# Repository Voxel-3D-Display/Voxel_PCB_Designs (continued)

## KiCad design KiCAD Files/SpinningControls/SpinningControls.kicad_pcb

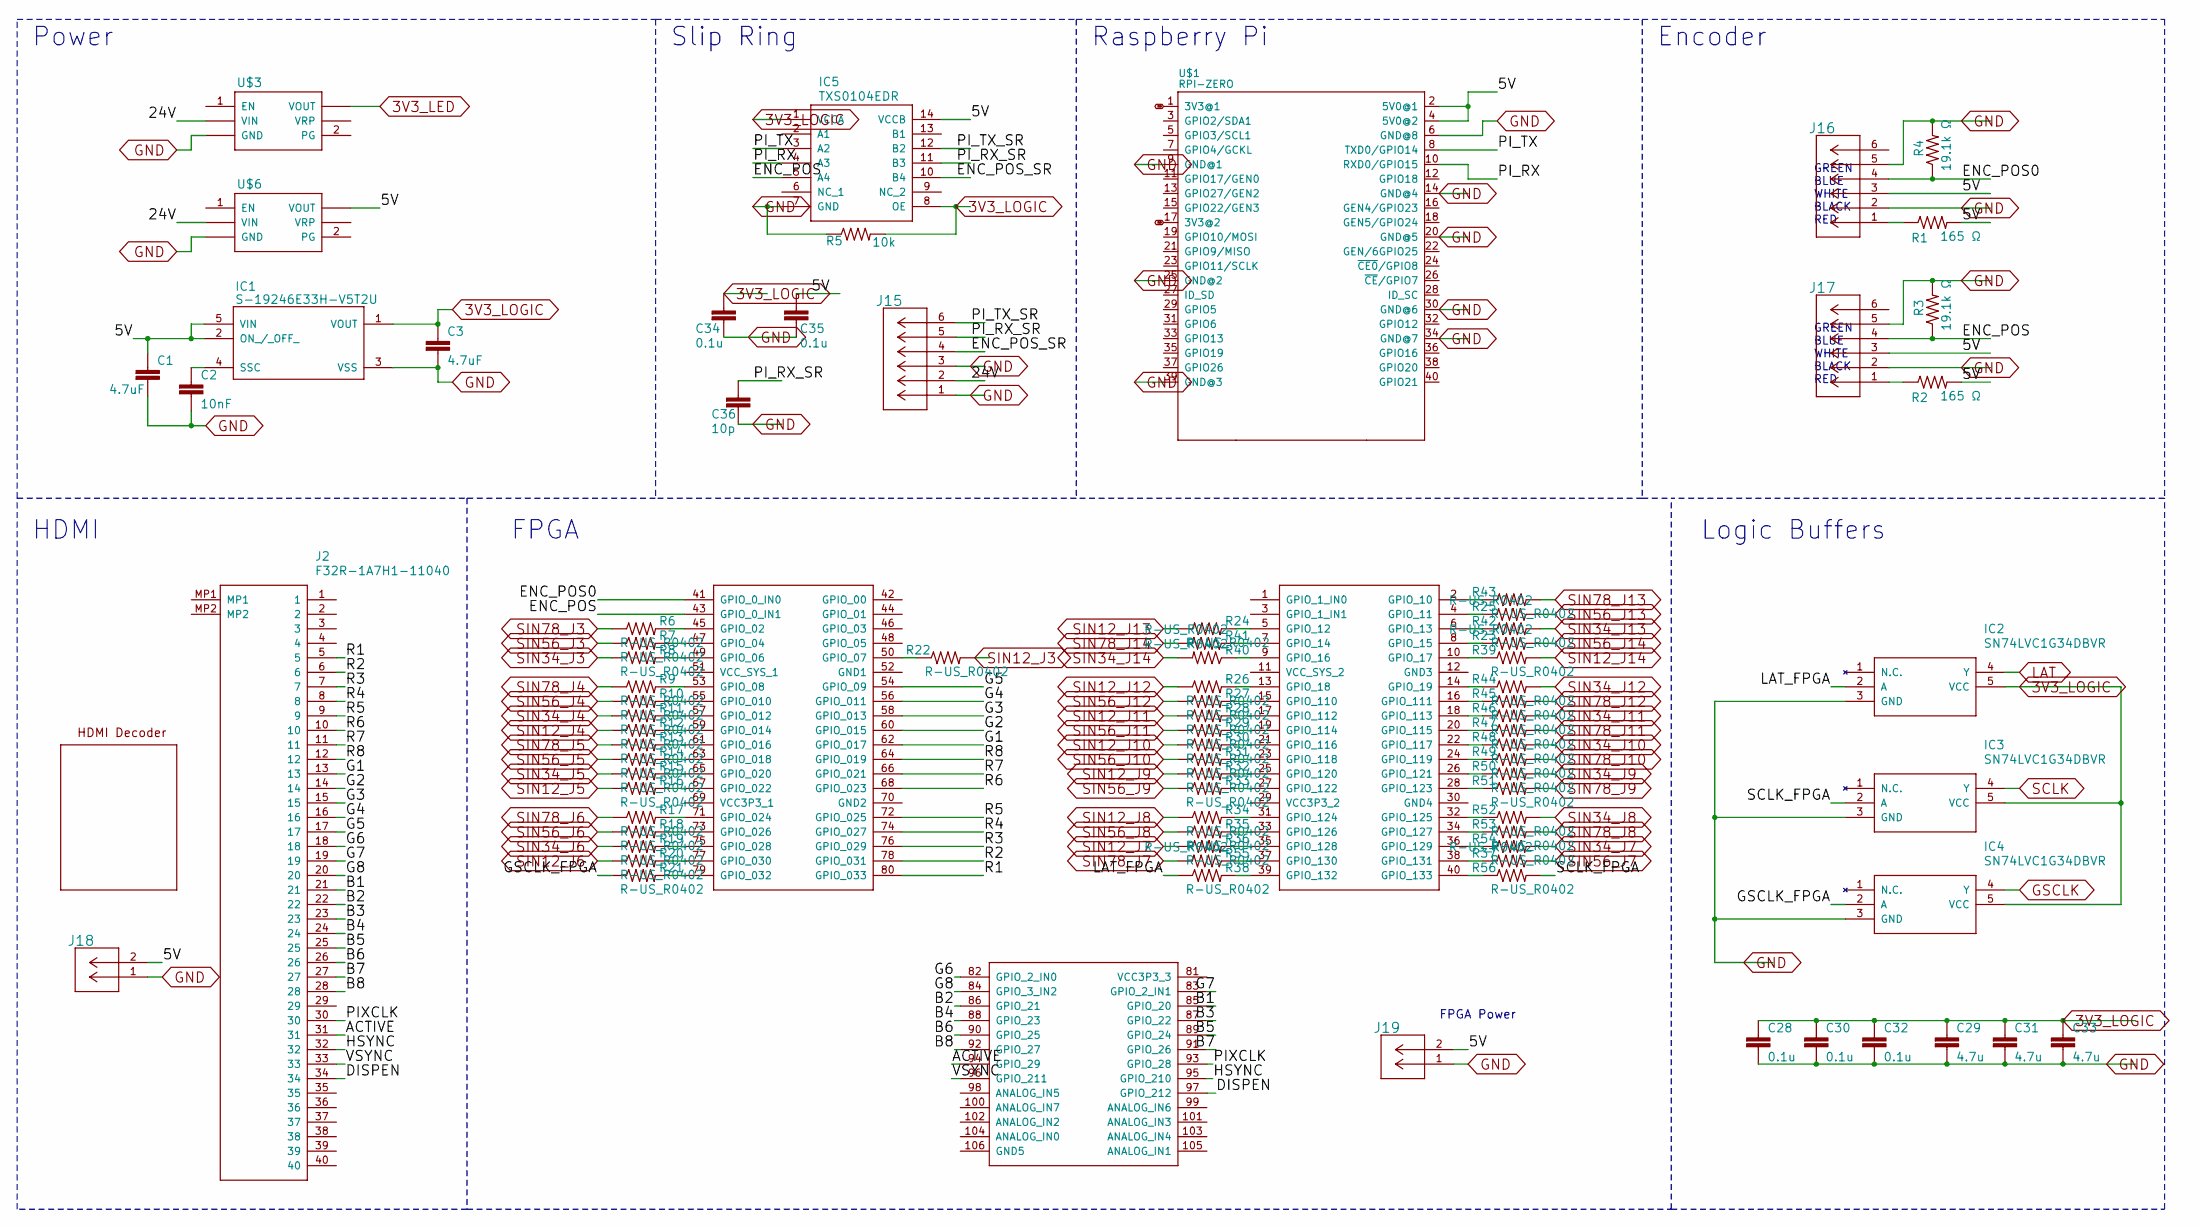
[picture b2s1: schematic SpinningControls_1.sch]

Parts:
C1, C3: 4.7uF; C0603
C2: 10nF; C0603
C28, C30, C32, C34, C35: 0.1u; C0603
C29, C31, C33: 4.7u; C0603
C36: 10p; C0603
FPGA: DE0-NANO
IC1: S-19246E33H-V5T2U; S19246E33HV5T2U
IC2, IC3, IC4: SN74LVC1G34DBVR; SOT95P280X145-5N
IC5: TXS0104EDR; SOIC127P600X175-14N
J2: F32R-1A7H1-11040; F32R1A7H111040
J15, J16, J17: 430450612; CON_430450612_MOL
J18, J19: 436500215; CON_436500215_MOL
R1, R2: 165 Ω; R0603
R3, R4: 19.1k Ω; R0603
R5: 10k; R0603
R6, R7, R8, R9, R10, R11, R12, R13, R14, R15, R16, R17, R18, R19, R20, R21, R22, R23, R24, R25, R26, R27, R28, R29, R30, R31, R32, R33, R34, R35, R36, R37, R38, R39, R40, R41, R42, R43, R44, R45, R46, R47, R48, R49, R50, R51, R52, R53, R54, R55, R56: R-US_R0402; R0402
U$1: RPI-ZERO; RASPBERRYPI_BASTELSTUBE_V13_RASPI_BOARD_B+_FULL
U$2: TFP401
U$3: 3V3_BUCK_REGULATOR; 2X06
U$6: 5V_BUCK_REGULATOR; 2X06

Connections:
3V3: U$1.1 (3V3@1), U$1.17 (3V3@2)
3V3_LED: U$3.11 (VOUT), U$3.12 (VOUT); also elsewhere on the board
3V3_LOGIC: C3.1, C28.1, C29.1, C30.1, C31.1, C32.1, C33.1, C34.1, IC1.1 (VOUT), IC2.5 (VCC), IC3.5 (VCC), IC4.5 (VCC), IC5.1 (VCCA), IC5.8 (OE), R5.2; also elsewhere on the board
/SpinningControls_1/5V: C1.1, C35.1, IC1.2 (ON_/_OFF_), IC1.5 (VIN), IC5.14 (VCCB), J16.3, J17.3, J18.2, J19.2, R1.2, R2.2, U$1.2 (5V0@1), U$1.4 (5V0@2), U$6.11 (VOUT), U$6.12 (VOUT)
/SpinningControls_1/24V: J15.2, U$3.5 (VIN), U$3.6 (VIN), U$6.5 (VIN), U$6.6 (VIN)
/SpinningControls_1/ACTIVE: J2.31; also elsewhere on the board
/SpinningControls_1/B1: J2.21; also elsewhere on the board
/SpinningControls_1/B2: J2.22; also elsewhere on the board
/SpinningControls_1/B3: J2.23; also elsewhere on the board
/SpinningControls_1/B4: J2.24; also elsewhere on the board
/SpinningControls_1/B5: J2.25; also elsewhere on the board
/SpinningControls_1/B6: J2.26; also elsewhere on the board
/SpinningControls_1/B7: J2.27; also elsewhere on the board
/SpinningControls_1/B8: J2.28; also elsewhere on the board
/SpinningControls_1/DISPEN: J2.34; also elsewhere on the board
/SpinningControls_1/ENC_POS: IC5.5 (A4), J17.4, R3.1; also elsewhere on the board
/SpinningControls_1/ENC_POS0: J16.4, R4.1; also elsewhere on the board
/SpinningControls_1/ENC_POS_SR: IC5.10 (B4), J15.4
/SpinningControls_1/G1: J2.13; also elsewhere on the board
/SpinningControls_1/G2: J2.14; also elsewhere on the board
/SpinningControls_1/G3: J2.15; also elsewhere on the board
/SpinningControls_1/G4: J2.16; also elsewhere on the board
/SpinningControls_1/G5: J2.17; also elsewhere on the board
/SpinningControls_1/G6: J2.18; also elsewhere on the board
/SpinningControls_1/G7: J2.19; also elsewhere on the board
/SpinningControls_1/G8: J2.20; also elsewhere on the board
/SpinningControls_1/GSCLK_FPGA: IC4.2 (A), R21.1
/SpinningControls_1/HSYNC: J2.32; also elsewhere on the board
/SpinningControls_1/LAT_FPGA: IC2.2 (A), R38.1
/SpinningControls_1/PIXCLK: J2.30; also elsewhere on the board
/SpinningControls_1/PI_RX: IC5.4 (A3), U$1.10 (RXD0/GPIO15)
/SpinningControls_1/PI_RX_SR: C36.1, IC5.11 (B3), J15.5
/SpinningControls_1/PI_TX: IC5.3 (A2), U$1.8 (TXD0/GPIO14)
/SpinningControls_1/PI_TX_SR: IC5.12 (B2), J15.6
/SpinningControls_1/R1: J2.5; also elsewhere on the board
/SpinningControls_1/R2: J2.6; also elsewhere on the board
/SpinningControls_1/R3: J2.7; also elsewhere on the board
/SpinningControls_1/R4: J2.8; also elsewhere on the board
/SpinningControls_1/R5: J2.9; also elsewhere on the board
/SpinningControls_1/R6: J2.10; also elsewhere on the board
/SpinningControls_1/R7: J2.11; also elsewhere on the board
/SpinningControls_1/R8: J2.12; also elsewhere on the board
/SpinningControls_1/SCLK_FPGA: IC3.2 (A), R56.2
/SpinningControls_1/VSYNC: J2.33; also elsewhere on the board
GND: C1.2, C2.2, C3.2, C28.2, C29.2, C30.2, C31.2, C32.2, C33.2, C34.2, C35.2, C36.2, IC1.3 (VSS), IC2.3 (GND), IC3.3 (GND), IC4.3 (GND), IC5.7 (GND), J15.1, J15.3, J16.2, J16.5, J17.2, J17.5, J18.1, J19.1, R3.2, R4.2, R5.1, U$1.6 (GND@8), U$1.9 (GND@1), U$1.14 (GND@4), U$1.20 (GND@5), U$1.25 (GND@2), U$1.30 (GND@6), U$1.34 (GND@7), U$1.39 (GND@3), U$3.7 (GND), U$3.8 (GND), U$3.9 (GND), U$3.10 (GND), U$6.7 (GND), U$6.8 (GND), U$6.9 (GND), U$6.10 (GND); also elsewhere on the board
GSCLK: IC4.4 (Y); also elsewhere on the board
LAT: IC2.4 (Y); also elsewhere on the board
unnamed: C2.1, IC1.4 (SSC)
unnamed 49: R43.1; also elsewhere on the board
unnamed 51: R25.2; also elsewhere on the board
unnamed 52: R24.2; also elsewhere on the board
unnamed 53: R42.1; also elsewhere on the board
unnamed 54: R41.1; also elsewhere on the board
unnamed 55: R23.2; also elsewhere on the board
unnamed 56: R40.1; also elsewhere on the board
unnamed 57: R39.1; also elsewhere on the board
unnamed 60: R26.2; also elsewhere on the board
unnamed 61: R44.1; also elsewhere on the board
unnamed 62: R27.2; also elsewhere on the board
unnamed 63: R45.1; also elsewhere on the board
unnamed 64: R28.2; also elsewhere on the board
unnamed 65: R46.1; also elsewhere on the board
unnamed 66: R29.2; also elsewhere on the board
unnamed 67: R47.1; also elsewhere on the board
unnamed 68: R30.2; also elsewhere on the board
unnamed 69: R48.1; also elsewhere on the board
unnamed 70: R31.2; also elsewhere on the board
unnamed 71: R49.1; also elsewhere on the board
unnamed 72: R32.2; also elsewhere on the board
unnamed 73: R50.1; also elsewhere on the board
unnamed 74: R33.2; also elsewhere on the board
unnamed 75: R51.1; also elsewhere on the board
unnamed 78: R34.2; also elsewhere on the board
unnamed 79: R52.1; also elsewhere on the board
unnamed 80: R35.2; also elsewhere on the board
unnamed 81: R53.1; also elsewhere on the board
unnamed 82: R36.2; also elsewhere on the board
unnamed 83: R54.1; also elsewhere on the board
unnamed 84: R55.1; also elsewhere on the board
unnamed 85: R37.2; also elsewhere on the board
unnamed 86: R38.2; also elsewhere on the board
unnamed 87: R56.1; also elsewhere on the board
unnamed 90: R6.2; also elsewhere on the board
unnamed 92: R7.2; also elsewhere on the board
unnamed 94: R8.2; also elsewhere on the board
unnamed 95: R22.1; also elsewhere on the board
unnamed 98: R9.2; also elsewhere on the board
unnamed 99: R10.2; also elsewhere on the board
unnamed 100: R11.2; also elsewhere on the board
unnamed 101: R12.2; also elsewhere on the board
unnamed 102: R13.2; also elsewhere on the board
unnamed 103: R14.2; also elsewhere on the board
unnamed 104: R15.2; also elsewhere on the board
unnamed 105: R16.2; also elsewhere on the board
unnamed 108: R17.2; also elsewhere on the board
unnamed 109: R18.2; also elsewhere on the board
unnamed 110: R19.2; also elsewhere on the board
unnamed 111: R20.2; also elsewhere on the board
unnamed 112: R21.2; also elsewhere on the board
unnamed: J16.1, R1.1
unnamed: J17.1, R2.1
unnamed: U$3.3 (VRP), U$3.4 (VRP)
unnamed: U$6.3 (VRP), U$6.4 (VRP)
SCLK: IC3.4 (Y); also elsewhere on the board
SIN12_J3: R22.2; also elsewhere on the board
SIN12_J4: R12.1; also elsewhere on the board
SIN12_J5: R16.1; also elsewhere on the board
SIN12_J6: R20.1; also elsewhere on the board
SIN12_J7: R36.1; also elsewhere on the board
SIN12_J8: R34.1; also elsewhere on the board
SIN12_J9: R32.1; also elsewhere on the board
SIN12_J10: R30.1; also elsewhere on the board
SIN12_J11: R28.1; also elsewhere on the board
SIN12_J12: R26.1; also elsewhere on the board
SIN12_J13: R24.1; also elsewhere on the board
SIN12_J14: R39.2; also elsewhere on the board
SIN34_J3: R8.1; also elsewhere on the board
SIN34_J4: R11.1; also elsewhere on the board
SIN34_J5: R15.1; also elsewhere on the board
SIN34_J6: R19.1; also elsewhere on the board
SIN34_J7: R54.2; also elsewhere on the board
SIN34_J8: R52.2; also elsewhere on the board
SIN34_J9: R50.2; also elsewhere on the board
SIN34_J10: R48.2; also elsewhere on the board
SIN34_J11: R46.2; also elsewhere on the board
SIN34_J12: R44.2; also elsewhere on the board
SIN34_J13: R42.2; also elsewhere on the board
SIN34_J14: R40.2; also elsewhere on the board
SIN56_J3: R7.1; also elsewhere on the board
SIN56_J4: R10.1; also elsewhere on the board
SIN56_J5: R14.1; also elsewhere on the board
SIN56_J6: R18.1; also elsewhere on the board
SIN56_J7: R37.1; also elsewhere on the board
SIN56_J8: R35.1; also elsewhere on the board
SIN56_J9: R33.1; also elsewhere on the board
SIN56_J10: R31.1; also elsewhere on the board
SIN56_J11: R29.1; also elsewhere on the board
SIN56_J12: R27.1; also elsewhere on the board
SIN56_J13: R25.1; also elsewhere on the board
SIN56_J14: R23.1; also elsewhere on the board
SIN78_J3: R6.1; also elsewhere on the board
SIN78_J4: R9.1; also elsewhere on the board
SIN78_J5: R13.1; also elsewhere on the board
SIN78_J6: R17.1; also elsewhere on the board
SIN78_J7: R55.2; also elsewhere on the board
SIN78_J8: R53.2; also elsewhere on the board
SIN78_J9: R51.2; also elsewhere on the board
SIN78_J10: R49.2; also elsewhere on the board
SIN78_J11: R47.2; also elsewhere on the board
SIN78_J12: R45.2; also elsewhere on the board
SIN78_J13: R43.2; also elsewhere on the board
SIN78_J14: R41.2; also elsewhere on the board

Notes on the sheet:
FPGA Power
GREEN BLUE WHITE BLACK RED
Raspberry Pi
Encoder
Slip Ring
Power
HDMI
FPGA
Logic Buffers

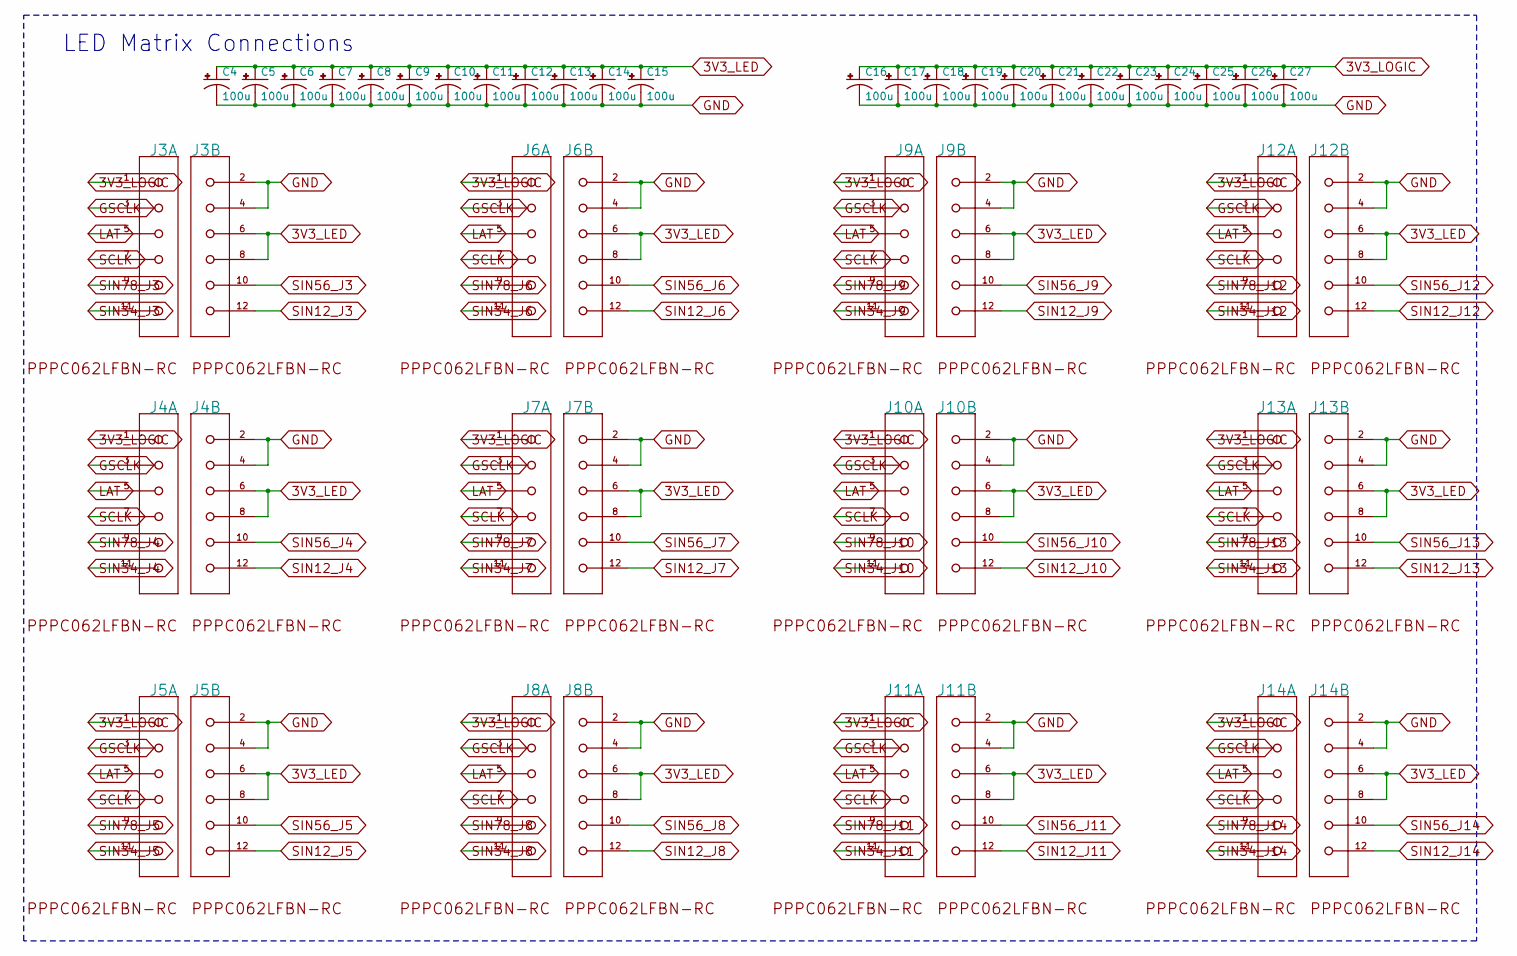
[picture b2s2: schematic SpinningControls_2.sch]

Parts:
C4, C5, C6, C7, C8, C9, C10, C11, C12, C13, C14, C15, C16, C17, C18, C19, C20, C21, C22, C23, C24, C25, C26, C27: 100u; E2-5
J3, J4, J5, J6, J7, J8, J9, J10, J11, J12, J13, J14: SULLINS_PPPC062LFBN-RCSULLINS_PPPC062LFBN-RC_0_0; SULLINS_PPPC062LFBN-RC_0

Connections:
3V3_LED: C4.+, C5.+, C6.+, C7.+, C8.+, C9.+, C10.+, C11.+, C12.+, C13.+, C14.+, C15.+, J3.6, J3.8, J4.6, J4.8, J5.6, J5.8, J6.6, J6.8, J7.6, J7.8, J8.6, J8.8, J9.6, J9.8, J10.6, J10.8, J11.6, J11.8, J12.6, J12.8, J13.6, J13.8, J14.6, J14.8; also elsewhere on the board
3V3_LOGIC: C16.+, C17.+, C18.+, C19.+, C20.+, C21.+, C22.+, C23.+, C24.+, C25.+, C26.+, C27.+, J3.1, J4.1, J5.1, J6.1, J7.1, J8.1, J9.1, J10.1, J11.1, J12.1, J13.1, J14.1; also elsewhere on the board
GND: C4.-, C5.-, C6.-, C7.-, C8.-, C9.-, C10.-, C11.-, C12.-, C13.-, C14.-, C15.-, C16.-, C17.-, C18.-, C19.-, C20.-, C21.-, C22.-, C23.-, C24.-, C25.-, C26.-, C27.-, J3.2, J3.4, J4.2, J4.4, J5.2, J5.4, J6.2, J6.4, J7.2, J7.4, J8.2, J8.4, J9.2, J9.4, J10.2, J10.4, J11.2, J11.4, J12.2, J12.4, J13.2, J13.4, J14.2, J14.4; also elsewhere on the board
GSCLK: J3.3, J4.3, J5.3, J6.3, J7.3, J8.3, J9.3, J10.3, J11.3, J12.3, J13.3, J14.3; also elsewhere on the board
LAT: J3.5, J4.5, J5.5, J6.5, J7.5, J8.5, J9.5, J10.5, J11.5, J12.5, J13.5, J14.5; also elsewhere on the board
SCLK: J3.7, J4.7, J5.7, J6.7, J7.7, J8.7, J9.7, J10.7, J11.7, J12.7, J13.7, J14.7; also elsewhere on the board
SIN12_J3: J3.12; also elsewhere on the board
SIN12_J4: J4.12; also elsewhere on the board
SIN12_J5: J5.12; also elsewhere on the board
SIN12_J6: J6.12; also elsewhere on the board
SIN12_J7: J7.12; also elsewhere on the board
SIN12_J8: J8.12; also elsewhere on the board
SIN12_J9: J9.12; also elsewhere on the board
SIN12_J10: J10.12; also elsewhere on the board
SIN12_J11: J11.12; also elsewhere on the board
SIN12_J12: J12.12; also elsewhere on the board
SIN12_J13: J13.12; also elsewhere on the board
SIN12_J14: J14.12; also elsewhere on the board
SIN34_J3: J3.11; also elsewhere on the board
SIN34_J4: J4.11; also elsewhere on the board
SIN34_J5: J5.11; also elsewhere on the board
SIN34_J6: J6.11; also elsewhere on the board
SIN34_J7: J7.11; also elsewhere on the board
SIN34_J8: J8.11; also elsewhere on the board
SIN34_J9: J9.11; also elsewhere on the board
SIN34_J10: J10.11; also elsewhere on the board
SIN34_J11: J11.11; also elsewhere on the board
SIN34_J12: J12.11; also elsewhere on the board
SIN34_J13: J13.11; also elsewhere on the board
SIN34_J14: J14.11; also elsewhere on the board
SIN56_J3: J3.10; also elsewhere on the board
SIN56_J4: J4.10; also elsewhere on the board
SIN56_J5: J5.10; also elsewhere on the board
SIN56_J6: J6.10; also elsewhere on the board
SIN56_J7: J7.10; also elsewhere on the board
SIN56_J8: J8.10; also elsewhere on the board
SIN56_J9: J9.10; also elsewhere on the board
SIN56_J10: J10.10; also elsewhere on the board
SIN56_J11: J11.10; also elsewhere on the board
SIN56_J12: J12.10; also elsewhere on the board
SIN56_J13: J13.10; also elsewhere on the board
SIN56_J14: J14.10; also elsewhere on the board
SIN78_J3: J3.9; also elsewhere on the board
SIN78_J4: J4.9; also elsewhere on the board
SIN78_J5: J5.9; also elsewhere on the board
SIN78_J6: J6.9; also elsewhere on the board
SIN78_J7: J7.9; also elsewhere on the board
SIN78_J8: J8.9; also elsewhere on the board
SIN78_J9: J9.9; also elsewhere on the board
SIN78_J10: J10.9; also elsewhere on the board
SIN78_J11: J11.9; also elsewhere on the board
SIN78_J12: J12.9; also elsewhere on the board
SIN78_J13: J13.9; also elsewhere on the board
SIN78_J14: J14.9; also elsewhere on the board

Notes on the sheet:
LED Matrix Connections

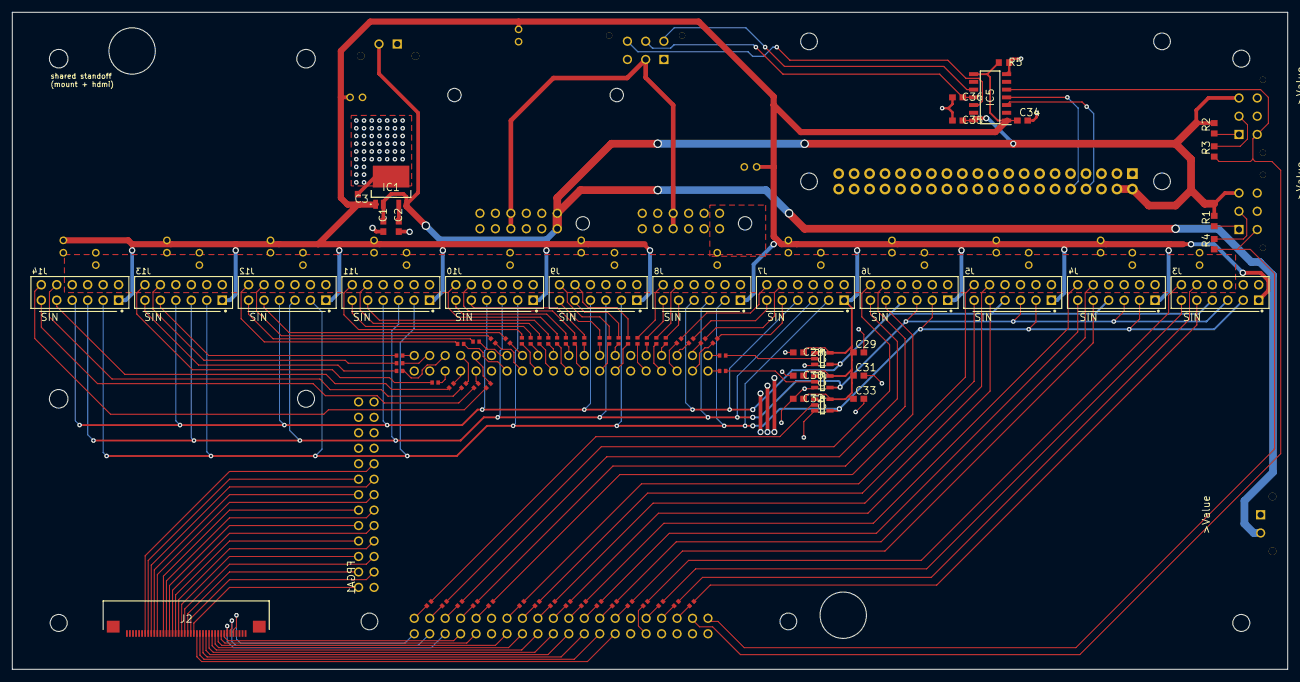
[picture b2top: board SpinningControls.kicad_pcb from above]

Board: 2 copper layers, 209.6 x 108.0 mm, 125 parts (0 on the bottom side), 152 nets.

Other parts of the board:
@HOLE0, @HOLE1, @HOLE2, @HOLE3, @HOLE4: (no value)
FPGA1: DE0-NANO

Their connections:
/SpinningControls_1/ACTIVE: FPGA1.94; also elsewhere on the board
/SpinningControls_1/B1: FPGA1.85; also elsewhere on the board
/SpinningControls_1/B2: FPGA1.86; also elsewhere on the board
/SpinningControls_1/B3: FPGA1.87; also elsewhere on the board
/SpinningControls_1/B4: FPGA1.88; also elsewhere on the board
/SpinningControls_1/B5: FPGA1.89; also elsewhere on the board
/SpinningControls_1/B6: FPGA1.90; also elsewhere on the board
/SpinningControls_1/B7: FPGA1.91; also elsewhere on the board
/SpinningControls_1/B8: FPGA1.92; also elsewhere on the board
/SpinningControls_1/DISPEN: FPGA1.97; also elsewhere on the board
/SpinningControls_1/ENC_POS: FPGA1.43; also elsewhere on the board
/SpinningControls_1/ENC_POS0: FPGA1.41; also elsewhere on the board
/SpinningControls_1/G1: FPGA1.62; also elsewhere on the board
/SpinningControls_1/G2: FPGA1.60; also elsewhere on the board
/SpinningControls_1/G3: FPGA1.58; also elsewhere on the board
/SpinningControls_1/G4: FPGA1.56; also elsewhere on the board
/SpinningControls_1/G5: FPGA1.54; also elsewhere on the board
/SpinningControls_1/G6: FPGA1.82; also elsewhere on the board
/SpinningControls_1/G7: FPGA1.83; also elsewhere on the board
/SpinningControls_1/G8: FPGA1.84; also elsewhere on the board
/SpinningControls_1/HSYNC: FPGA1.95; also elsewhere on the board
/SpinningControls_1/PIXCLK: FPGA1.93; also elsewhere on the board
/SpinningControls_1/R1: FPGA1.80; also elsewhere on the board
/SpinningControls_1/R2: FPGA1.78; also elsewhere on the board
/SpinningControls_1/R3: FPGA1.76; also elsewhere on the board
/SpinningControls_1/R4: FPGA1.74; also elsewhere on the board
/SpinningControls_1/R5: FPGA1.72; also elsewhere on the board
/SpinningControls_1/R6: FPGA1.68; also elsewhere on the board
/SpinningControls_1/R7: FPGA1.66; also elsewhere on the board
/SpinningControls_1/R8: FPGA1.64; also elsewhere on the board
/SpinningControls_1/VSYNC: FPGA1.96; also elsewhere on the board
unnamed 49: FPGA1.2; also elsewhere on the board
unnamed 51: FPGA1.4; also elsewhere on the board
unnamed 52: FPGA1.5; also elsewhere on the board
unnamed 53: FPGA1.6; also elsewhere on the board
unnamed 54: FPGA1.7; also elsewhere on the board
unnamed 55: FPGA1.8; also elsewhere on the board
unnamed 56: FPGA1.9; also elsewhere on the board
unnamed 57: FPGA1.10; also elsewhere on the board
unnamed 60: FPGA1.13; also elsewhere on the board
unnamed 61: FPGA1.14; also elsewhere on the board
unnamed 62: FPGA1.15; also elsewhere on the board
unnamed 63: FPGA1.16; also elsewhere on the board
unnamed 64: FPGA1.17; also elsewhere on the board
unnamed 65: FPGA1.18; also elsewhere on the board
unnamed 66: FPGA1.19; also elsewhere on the board
unnamed 67: FPGA1.20; also elsewhere on the board
unnamed 68: FPGA1.21; also elsewhere on the board
unnamed 69: FPGA1.22; also elsewhere on the board
unnamed 70: FPGA1.23; also elsewhere on the board
unnamed 71: FPGA1.24; also elsewhere on the board
unnamed 72: FPGA1.25; also elsewhere on the board
unnamed 73: FPGA1.26; also elsewhere on the board
unnamed 74: FPGA1.27; also elsewhere on the board
unnamed 75: FPGA1.28; also elsewhere on the board
unnamed 78: FPGA1.31; also elsewhere on the board
unnamed 79: FPGA1.32; also elsewhere on the board
unnamed 80: FPGA1.33; also elsewhere on the board
unnamed 81: FPGA1.34; also elsewhere on the board
unnamed 82: FPGA1.35; also elsewhere on the board
unnamed 83: FPGA1.36; also elsewhere on the board
unnamed 84: FPGA1.37; also elsewhere on the board
unnamed 85: FPGA1.38; also elsewhere on the board
unnamed 86: FPGA1.39; also elsewhere on the board
unnamed 87: FPGA1.40; also elsewhere on the board
unnamed 90: FPGA1.45; also elsewhere on the board
unnamed 92: FPGA1.47; also elsewhere on the board
unnamed 94: FPGA1.49; also elsewhere on the board
unnamed 95: FPGA1.50; also elsewhere on the board
unnamed 98: FPGA1.53; also elsewhere on the board
unnamed 99: FPGA1.55; also elsewhere on the board
unnamed 100: FPGA1.57; also elsewhere on the board
unnamed 101: FPGA1.59; also elsewhere on the board
unnamed 102: FPGA1.61; also elsewhere on the board
unnamed 103: FPGA1.63; also elsewhere on the board
unnamed 104: FPGA1.65; also elsewhere on the board
unnamed 105: FPGA1.67; also elsewhere on the board
unnamed 108: FPGA1.71; also elsewhere on the board
unnamed 109: FPGA1.73; also elsewhere on the board
unnamed 110: FPGA1.75; also elsewhere on the board
unnamed 111: FPGA1.77; also elsewhere on the board
unnamed 112: FPGA1.79; also elsewhere on the board

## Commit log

2021-10-13 Initial High Density PCB
2021-10-21 Automated Python scripts and one block of LED matrix
    Added a bunch of python scripts for automating Eagle design. Created a template for one LED driver block of board (to be copied later)
2021-10-28 added pictures of led matrix pcbs
2021-11-06 Finished placing all LEDs and Led Drivers
2021-11-06 Routed all the signals from the FPGA
2021-11-10 Finished routing traces on high density matrix PCB
2021-11-10 High density PCB fixes
    Fixed airwires errors and grouped components on schematic
2022-01-14 Finalized LED Matrix schematic and board files
2022-01-14 gerber files generated; cleanup
2022-01-15 fixed problem of not having pairs of drivers daisy-chained
2022-01-22 created rev2 for high density led matrix PCB
2022-01-22 lib additions for controls pcb
2022-01-22 Added RasPi EAGLE Lib
2022-01-23 Added Pololu buck regulators
2022-01-23 more lib additions
2022-01-23 Added DE0-Nano
2022-01-23 Added logic buffer
2022-01-23 power schematic and library additions
2022-01-24 finished rev 2 of PCB submatrix led
2022-01-30 controls layout partial
2022-01-30 parts exchange, layout corrections, no routing
2022-01-30 Fixed encoder on spinning controls board
2022-01-31 Added Motor Controller PCB
2022-01-31 Added button input
2022-01-31 schem FPGA pins, partial
2022-01-31 full schematic, silkscreen cleanup
2022-01-31 Started some traces
2022-01-31 Updated Eagle Lib
2022-01-31 Finished power routing and other minor changes
2022-01-31 Finished controls board, added gerbers
2022-01-31 Cleaned schematics, added pdfs
2022-01-31 Added some silk screen
2022-01-31 Updated pinouts to align with control board
2022-01-31 reuploaded gerber files
2022-01-31 added pdf schematic of led matrix pcb
2022-02-01 Added logic buffers to LED matrix
2022-02-01 Fixes to controls board
2022-02-01 routed logic buffers on matrix pcb
2022-02-01 Added logic level shifter
2022-02-01 dan changes + lib
2022-02-01 fixed soldermask on led submatrix
2022-02-01 dan tings, 50ohm FPGA inline, 3v3 to 5 logic for SR
2022-02-01 to-kyle documentation updates
2022-02-01 full routing layout and schematic
2022-02-01 added mounting holes; processed CAM and schem PDF
2022-03-18 silkscreen update
2022-03-18 fixed gerbers
2022-03-18 bleck
2022-03-18 added v3 of submatrix PCB
2022-03-19 Added newly ordered controls board gerbers
2022-03-30 renamed 2x13 header silk screen
2022-04-16 Added KiCAD Files
